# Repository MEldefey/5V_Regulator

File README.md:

# 5V_Regulator
السلام عليكم (peace upon you !)🌹🫡
my name is Mahmoud Eldefey i am student study the faculty of mechatronics Engineering and work side by side as a freelancer in many feilds in real [Mechnical design -Electrical Design -Programing Language - Microcontoler Programing -IOT systems - simualtion design - Graphics design - video editing - data enty - Technical Writing ]
i am happy to share that i finshed worked on this PCB that have my own logo i learn somethings new about designing and how to work with KIcad software which is a really awsome free opensource software but it still need some library 
 that 's a 5V regulator circuit , it can take 5-12V and give 5V as an output 
 if you need any help i will be happy to help 🫡🌹
  this projct help me to reach to build a power supply 
  which i will upload soon  
  happy to help 
  see you next time 👋

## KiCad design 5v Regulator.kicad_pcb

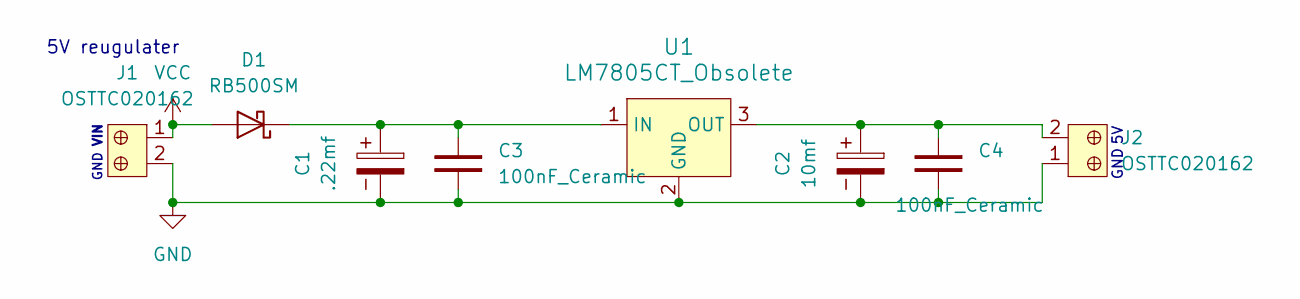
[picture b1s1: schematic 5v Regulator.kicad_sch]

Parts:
C1: .22mf; CP_Radial_D4.0mm_P2.00mm
C2: 10mf; CP_Radial_D4.0mm_P2.00mm
C3, C4: 100nF_Ceramic; C_Disc_D5.0mm_W2.5mm_P2.50mm
D1: RB500SM; D_SOD-523; Part Number RB500SM-30FHT2R
J1, J2: OSTTC020162; Term_Block_1x2_P5mm; MPN OSTTC020162; Digi-Key_PN ED2600-ND
U1: LM7805CT_Obsolete; TO-220-3; MPN LM7805CT; Digi-Key_PN LM7805CT-ND

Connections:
+5V: C2.1, C4.1, J2.2, U1.3 (OUT)
unnamed: D1.2 (A), J1.1
unnamed: C1.1, C3.1, D1.1 (K), U1.1 (IN)
unnamed: C1.2, C2.2, C3.2, C4.2, J1.2, J2.1, U1.2 (GND)

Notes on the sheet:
GND
5V reugulater
VIN
GND

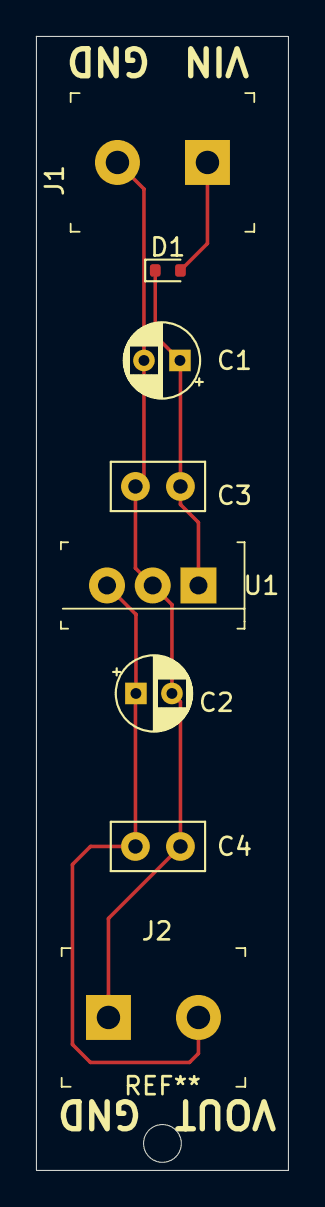
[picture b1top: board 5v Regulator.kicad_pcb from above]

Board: 2 copper layers, 14.0 x 63.0 mm, 8 parts (0 on the bottom side), 4 nets.

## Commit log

2025-04-10 first_commit
